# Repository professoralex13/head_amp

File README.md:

# CosplayCore

TODO: Put information about it here

## IMPORTANT NOTES:
Main board V1.0 runs ADC data from a CODEC into GPIO12 which also serves as a strapping pin. This signal is pulled high by the CODEC resulting in the ESP32 booting with a flash chip voltage is 1.8V which is incorrect.
To work around this, the following command must be run:
```espefuse --port [PORT] burn-efuse XPD_SDIO_REG 1 XPD_SDIO_TIEH 1 XPD_SDIO_FORCE 1```

This overrides the strapping pin so the memory supply voltage is permenantly set at 3.3V.
Until this comand is run and the fuses are burned on the ESP32, it cannot be flashed with any code.

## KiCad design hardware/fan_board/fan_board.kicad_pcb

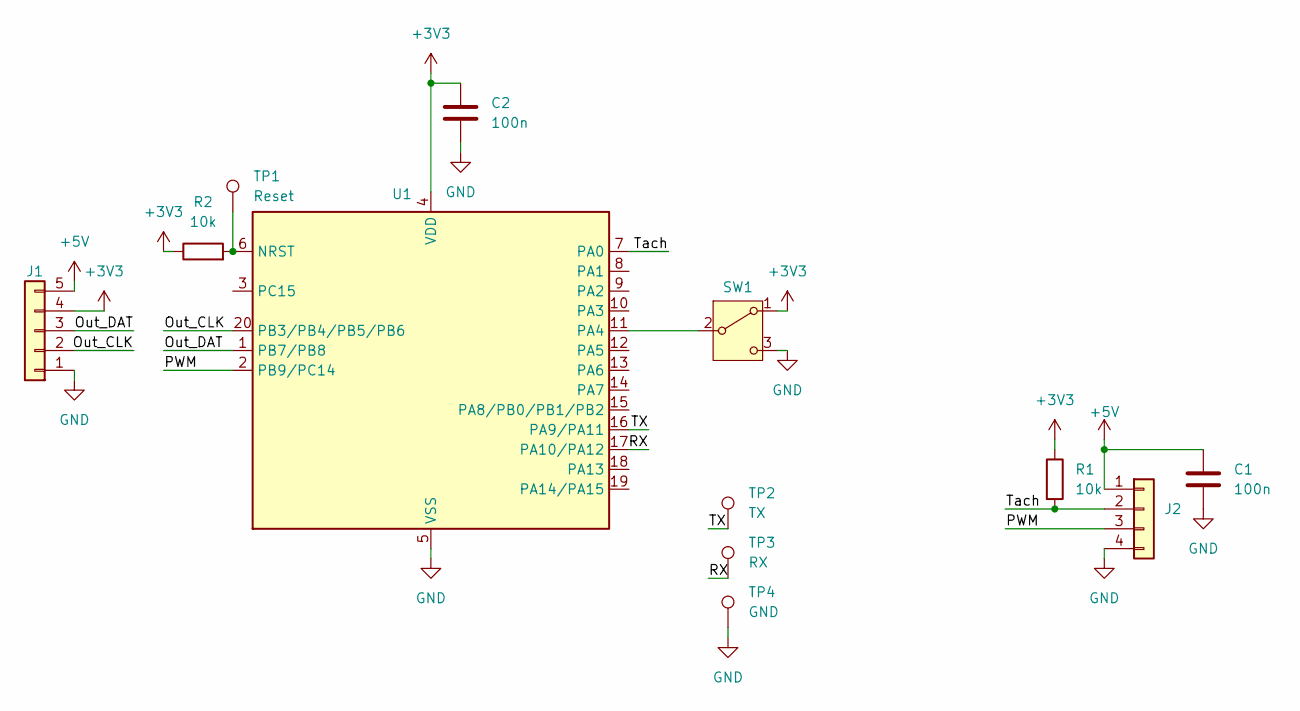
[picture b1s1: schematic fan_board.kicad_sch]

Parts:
C1, C2: 100n; C_1206_3216Metric_Pad1.33x1.80mm_HandSolder; LCSC C24497
J1: Conn_01x05; JST_EH_S5B-EH_1x05_P2.50mm_Horizontal; LCSC C265103
J2: Conn_01x04; JST_EH_S4B-EH_1x04_P2.50mm_Horizontal; LCSC C265068
R1, R2: 10k; R_1206_3216Metric_Pad1.30x1.75mm_HandSolder; LCSC C17902
SW1: SW_SPDT; Nidec_Copal_CAS-120A; LCSC C5619548
TP1: Reset; TestPoint_Pad_3.0x3.0mm
TP2: TX; TestPoint_Pad_3.0x3.0mm
TP3: RX; TestPoint_Pad_3.0x3.0mm
TP4: GND; TestPoint_Pad_3.0x3.0mm
U1: STM32G030F6Px; TSSOP-20_4.4x6.5mm_P0.65mm; LCSC C529330

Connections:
+3V3: C2.1, J1.4, R1.1, R2.1, SW1.1 (A), U1.4 (VDD)
+5V: C1.1, J1.5, J2.1
/Out_CLK: J1.2, U1.20 (PB3/PB4/PB5/PB6)
/Out_DAT: J1.3, U1.1 (PB7/PB8)
/PWM: J2.3, U1.2 (PB9/PC14)
/RX: TP3.1, U1.17 (PA10/PA12)
/TX: TP2.1, U1.16 (PA9/PA11)
/Tach: J2.2, R1.2, U1.7 (PA0)
GND: C1.2, C2.2, J1.1, J2.4, SW1.3 (C), TP4.1, U1.5 (VSS)
unnamed: SW1.2 (B), U1.11 (PA4)
unnamed: R2.2, TP1.1, U1.6 (NRST)

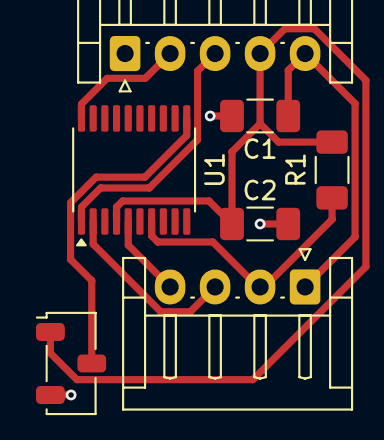
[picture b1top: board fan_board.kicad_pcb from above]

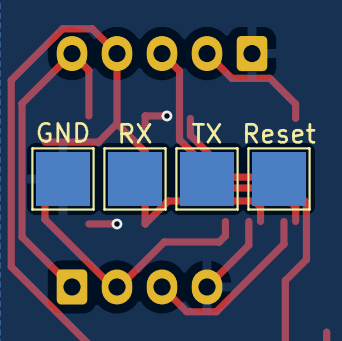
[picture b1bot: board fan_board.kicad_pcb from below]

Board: 2 copper layers, 11 parts (4 on the bottom side), 11 nets.

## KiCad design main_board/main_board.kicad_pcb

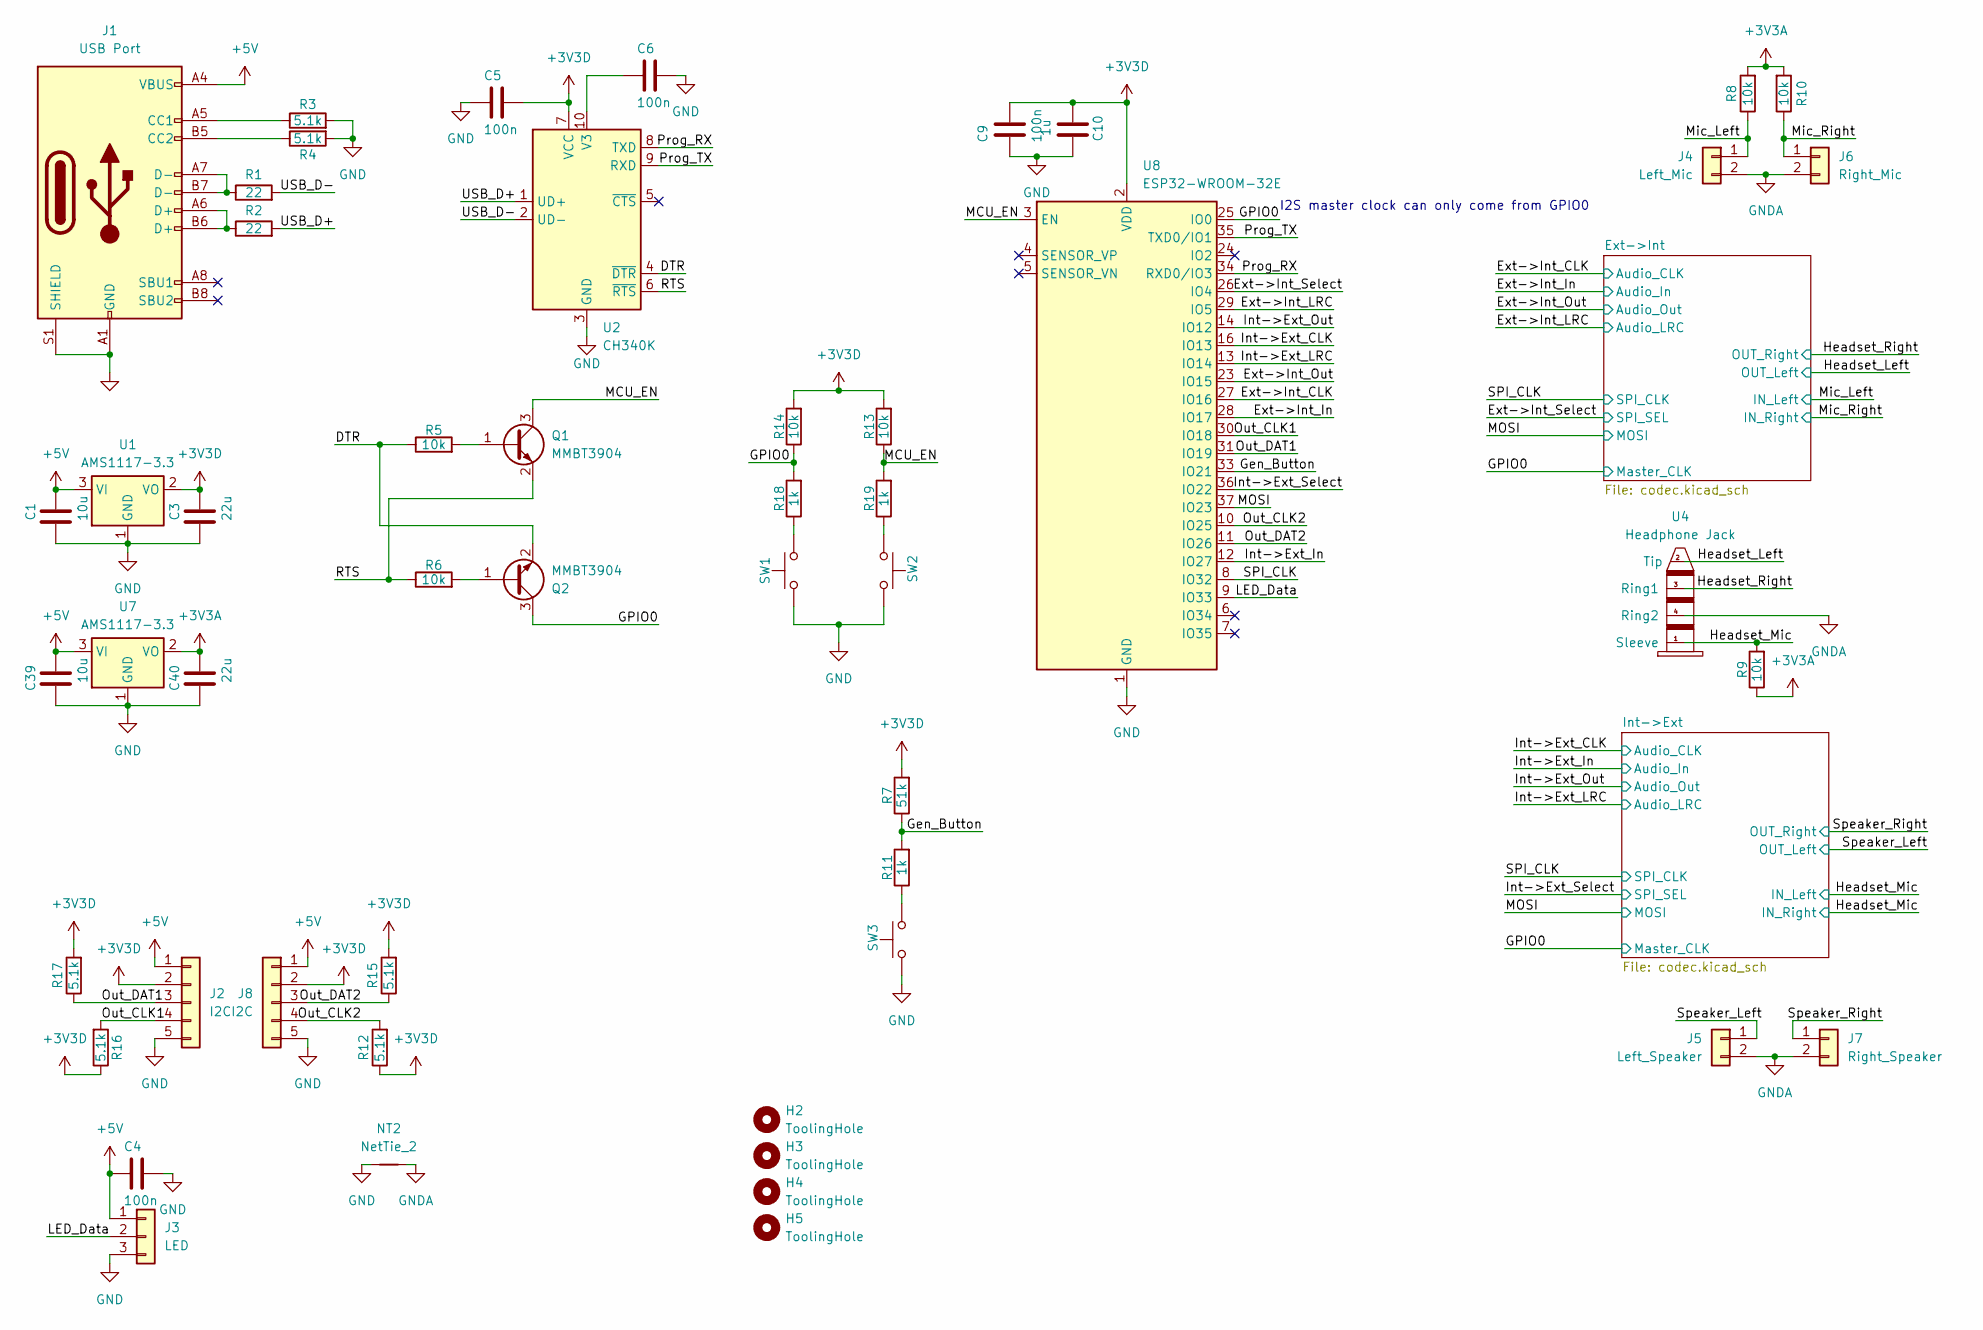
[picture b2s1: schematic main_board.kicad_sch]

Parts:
C1, C39: 10u; C_0603_1608Metric; LCSC C19702
C3, C40: 22u; C_0603_1608Metric; LCSC C59461
C4, C5, C6: 100n; C_0402_1005Metric; LCSC C307331
C9: 100n; C_0603_1608Metric; LCSC C14663
C10: 1u; C_0603_1608Metric; LCSC C15849
H2, H3, H4, H5: ToolingHole; ToolingHole_1.152mm
J1: USB Port; USB_C_Receptacle_GCT_USB4105-xx-A_16P_TopMnt_Horizontal; LCSC C2927038
J2, J8: I2C; JST_EH_S5B-EH_1x05_P2.50mm_Horizontal; LCSC C265103
J3: LED; JST_EH_S3B-EH_1x03_P2.50mm_Horizontal; LCSC C263754
J4: Left_Mic; JST_EH_S2B-EH_1x02_P2.50mm_Horizontal; LCSC C514173
J5: Left_Speaker; JST_EH_S2B-EH_1x02_P2.50mm_Horizontal; LCSC C514173
J6: Right_Mic; JST_EH_S2B-EH_1x02_P2.50mm_Horizontal; LCSC C514173
J7: Right_Speaker; JST_EH_S2B-EH_1x02_P2.50mm_Horizontal; LCSC C514173
NT2: NetTie_2; NetTie-2_SMD_Pad2.0mm
Q1, Q2: MMBT3904; SOT-23; LCSC C20526
R1, R2: 22; R_0402_1005Metric; LCSC C25092
R3, R4, R12, R15, R16, R17: 5.1k; R_0402_1005Metric; LCSC C25905
R5, R6, R8, R9, R10, R13, R14: 10k; R_0402_1005Metric; LCSC C25744
R7: 51k; R_0402_1005Metric; LCSC C25794
R11, R18, R19: 1k; R_0402_1005Metric; LCSC C11702
SW1, SW2, SW3: SW_Push; SW_SPST_TS-1088-xR020; LCSC C720477
U1, U7: AMS1117-3.3; SOT-223-3_TabPin2; LCSC C6186
U2: CH340K; SSOP-10-1EP_3.9x4.9mm_P1mm_EP2.1x3.3mm; LCSC C18208922
U4: Headphone Jack; PJ-320A; LCSC C2884926
U8: ESP32-WROOM-32E; LCSC C701342

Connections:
+3V3A: C40.2, R8.2, R9.1, R10.2, U7.2 (VO); also elsewhere on the board
+3V3D: C3.2, C5.2, C9.2, C10.1, J2.2, J8.2, R7.2, R12.1, R13.2, R14.2, R15.2, R16.1, R17.2, U1.2 (VO), U2.7 (VCC), U8.2 (VDD); also elsewhere on the board
+5V: C1.2, C4.1, C39.2, J1.A4 (VBUS), J1.A9 (VBUS), J1.B4 (VBUS), J1.B9 (VBUS), J2.1, J3.1, J8.1, U1.3 (VI), U7.3 (VI)
/DTR: Q2.2 (E), R5.1, U2.4 (~DTR)
/Ext->Int_CLK: U8.27 (IO16); also elsewhere on the board
/Ext->Int_In: U8.28 (IO17); also elsewhere on the board
/Ext->Int_LRC: U8.29 (IO5); also elsewhere on the board
/Ext->Int_Out: U8.23 (IO15); also elsewhere on the board
/Ext->Int_Select: U8.26 (IO4); also elsewhere on the board
/GPIO0: Q2.3 (C), R14.1, R18.2, U8.25 (IO0); also elsewhere on the board
/Gen_Button: R7.1, R11.2, U8.33 (IO21)
/Headset_Left: U4.2 (Tip); also elsewhere on the board
/Headset_Mic: R9.2, U4.1 (Sleeve); also elsewhere on the board
/Headset_Right: U4.3 (Ring1); also elsewhere on the board
/Int->Ext_CLK: U8.16 (IO13); also elsewhere on the board
/Int->Ext_In: U8.12 (IO27); also elsewhere on the board
/Int->Ext_LRC: U8.13 (IO14); also elsewhere on the board
/Int->Ext_Out: U8.14 (IO12); also elsewhere on the board
/Int->Ext_Select: U8.36 (IO22); also elsewhere on the board
/LED_Data: J3.2, U8.9 (IO33)
/MCU_EN: Q1.3 (C), R13.1, R19.2, U8.3 (EN)
/MOSI: U8.37 (IO23); also elsewhere on the board
/Mic_Left: J4.1, R8.1; also elsewhere on the board
/Mic_Right: J6.1, R10.1; also elsewhere on the board
/Out_CLK1: J2.4, R16.2, U8.30 (IO18)
/Out_CLK2: J8.4, R12.2, U8.10 (IO25)
/Out_DAT1: J2.3, R17.1, U8.31 (IO19)
/Out_DAT2: J8.3, R15.1, U8.11 (IO26)
/Prog_RX: U2.8 (TXD), U8.34 (RXD0/IO3)
/Prog_TX: U2.9 (RXD), U8.35 (TXD0/IO1)
/RTS: Q1.2 (E), R6.1, U2.6 (~RTS)
/SPI_CLK: U8.8 (IO32); also elsewhere on the board
/Speaker_Left: J5.1; also elsewhere on the board
/Speaker_Right: J7.1; also elsewhere on the board
/USB_D+: R2.2, U2.1 (UD+)
/USB_D-: R1.2, U2.2 (UD-)
GND: C1.1, C3.1, C4.2, C5.1, C6.2, C9.1, C10.2, C39.1, C40.1, J1.A1 (GND), J1.A12 (GND), J1.B1 (GND), J1.B12 (GND), J1.S1 (SHIELD), J2.5, J3.3, J8.5, NT2.1, R3.2, R4.2, SW1.1, SW2.1, SW3.1, U1.1 (GND), U2.3 (GND), U2.11 (GND), U7.1 (GND), U8.1 (GND), U8.15 (GND), U8.38 (GND), U8.39 (GND); also elsewhere on the board
GNDA: J4.2, J5.2, J6.2, J7.2, NT2.2, U4.4 (Ring2); also elsewhere on the board
unnamed: J1.A5 (CC1), R3.1
unnamed: J1.B5 (CC2), R4.1
unnamed: J1.A6 (D+), J1.B6 (D+), R2.1
unnamed: J1.A7 (D-), J1.B7 (D-), R1.1
unnamed: Q1.1 (B), R5.2
unnamed: Q2.1 (B), R6.2
unnamed: R11.1, SW3.2
unnamed: R18.1, SW1.2
unnamed: R19.1, SW2.2
unnamed: C6.1, U2.10 (V3)

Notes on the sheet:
I2S master clock can only come from GPIO0

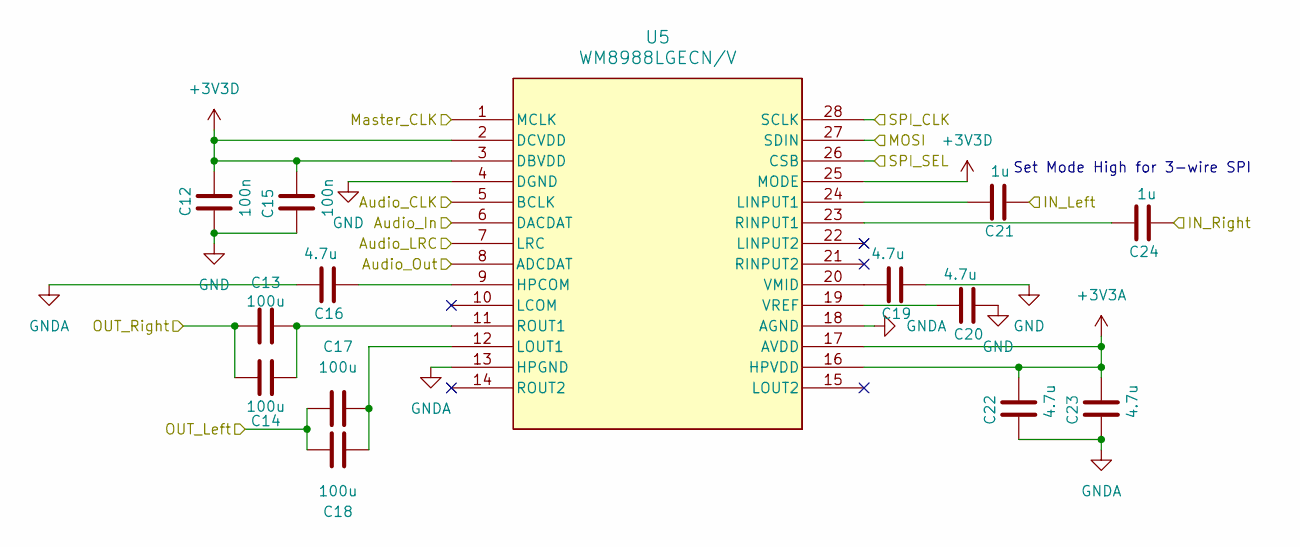
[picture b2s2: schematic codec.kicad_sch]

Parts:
C12, C15: 100n; C_0402_1005Metric; LCSC C307331
C13, C14, C17, C18: 100u; C_1206_3216Metric; LCSC C15008
C16, C19, C20, C22, C23: 4.7u; C_0402_1005Metric; LCSC C23733
C21, C24: 1u; C_0402_1005Metric; LCSC C52923
U5: WM8988LGECN/V; QFN28_4X4_CIR; LCSC C323851

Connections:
+3V3A: C22.2, C23.2, U5.16 (HPVDD), U5.17 (AVDD); also elsewhere on the board
+3V3D: C12.2, C15.2, U5.2 (DCVDD), U5.3 (DBVDD), U5.25 (MODE); also elsewhere on the board
/GPIO0: U5.1 (MCLK); also elsewhere on the board
/Headset_Mic: C21.1, C24.1; also elsewhere on the board
/Int->Ext_CLK: U5.5 (BCLK); also elsewhere on the board
/Int->Ext_In: U5.6 (DACDAT); also elsewhere on the board
/Int->Ext_LRC: U5.7 (LRC); also elsewhere on the board
/Int->Ext_Out: U5.8 (ADCDAT); also elsewhere on the board
/Int->Ext_Select: U5.26 (CSB); also elsewhere on the board
/MOSI: U5.27 (SDIN); also elsewhere on the board
/SPI_CLK: U5.28 (SCLK); also elsewhere on the board
/Speaker_Left: C17.1, C18.1; also elsewhere on the board
/Speaker_Right: C13.1, C14.1; also elsewhere on the board
GND: C12.1, C15.1, C19.1, C20.1, U5.4 (DGND); also elsewhere on the board
GNDA: C16.2, C22.1, C23.1, U5.13 (HPGND), U5.18 (AGND); also elsewhere on the board
unnamed: C16.1, U5.9 (HPCOM)
unnamed: C21.2, U5.24 (LINPUT1)
unnamed: C17.2, C18.2, U5.12 (LOUT1)
unnamed: C24.2, U5.23 (RINPUT1)
unnamed: C13.2, C14.2, U5.11 (ROUT1)
unnamed: C19.2, U5.20 (VMID)
unnamed: C20.2, U5.19 (VREF)

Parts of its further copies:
C25, C28: 100n; C_0402_1005Metric; LCSC C307331
C26, C27, C30, C31: 100u; C_1206_3216Metric; LCSC C15008
C29, C32, C33, C35, C36: 4.7u; C_0402_1005Metric; LCSC C23733
C34, C37: 1u; C_0402_1005Metric; LCSC C52923
U6: WM8988LGECN/V; QFN28_4X4_CIR; LCSC C323851

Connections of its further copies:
+3V3A: C35.2, C36.2, U6.16 (HPVDD), U6.17 (AVDD); also elsewhere on the board
+3V3D: C25.2, C28.2, U6.2 (DCVDD), U6.3 (DBVDD), U6.25 (MODE); also elsewhere on the board
/Ext->Int_CLK: U6.5 (BCLK); also elsewhere on the board
/Ext->Int_In: U6.6 (DACDAT); also elsewhere on the board
/Ext->Int_LRC: U6.7 (LRC); also elsewhere on the board
/Ext->Int_Out: U6.8 (ADCDAT); also elsewhere on the board
/Ext->Int_Select: U6.26 (CSB); also elsewhere on the board
/GPIO0: U6.1 (MCLK); also elsewhere on the board
/Headset_Left: C30.1, C31.1; also elsewhere on the board
/Headset_Right: C26.1, C27.1; also elsewhere on the board
/MOSI: U6.27 (SDIN); also elsewhere on the board
/Mic_Left: C34.1; also elsewhere on the board
/Mic_Right: C37.1; also elsewhere on the board
/SPI_CLK: U6.28 (SCLK); also elsewhere on the board
GND: C25.1, C28.1, C32.1, C33.1, U6.4 (DGND); also elsewhere on the board
GNDA: C29.2, C35.1, C36.1, U6.13 (HPGND), U6.18 (AGND); also elsewhere on the board
unnamed: C29.1, U6.9 (HPCOM)
unnamed: C34.2, U6.24 (LINPUT1)
unnamed: C30.2, C31.2, U6.12 (LOUT1)
unnamed: C37.2, U6.23 (RINPUT1)
unnamed: C26.2, C27.2, U6.11 (ROUT1)
unnamed: C32.2, U6.20 (VMID)
unnamed: C33.2, U6.19 (VREF)

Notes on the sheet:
Set Mode High for 3-wire SPI

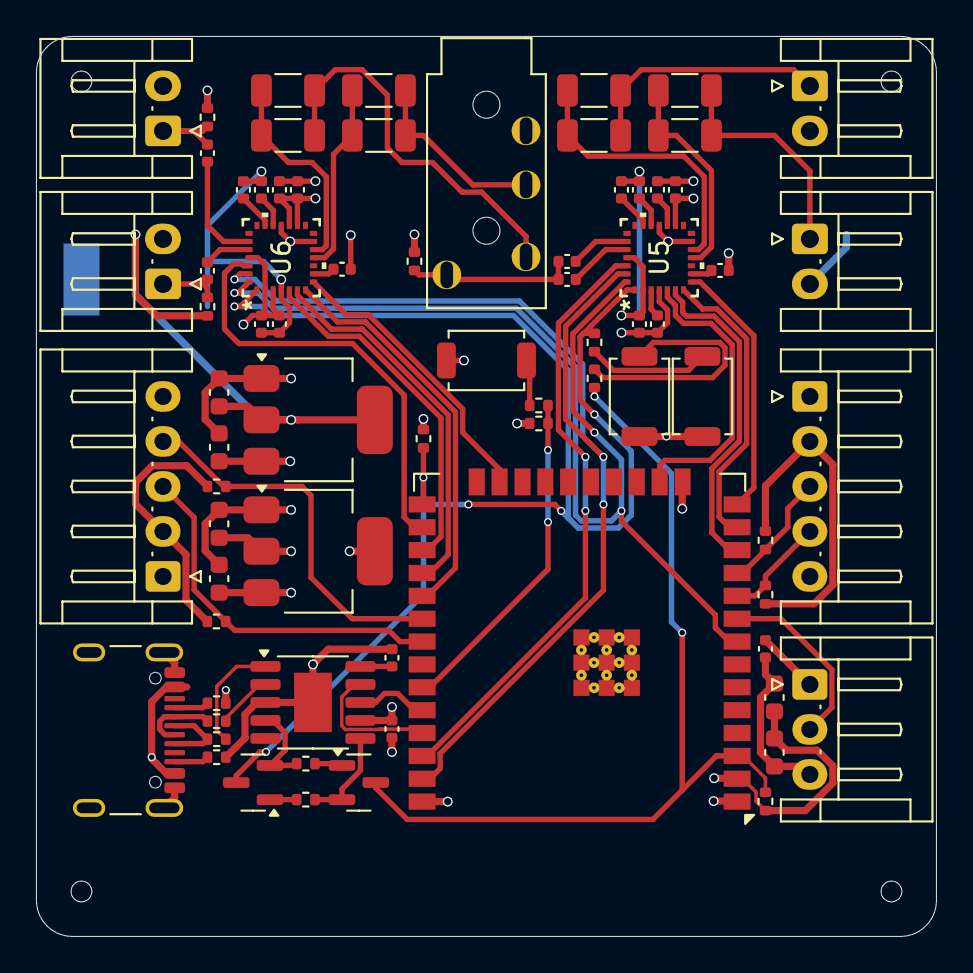
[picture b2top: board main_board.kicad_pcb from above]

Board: 4 copper layers, 50.0 x 50.0 mm, 79 parts (1 on the bottom side), 62 nets.

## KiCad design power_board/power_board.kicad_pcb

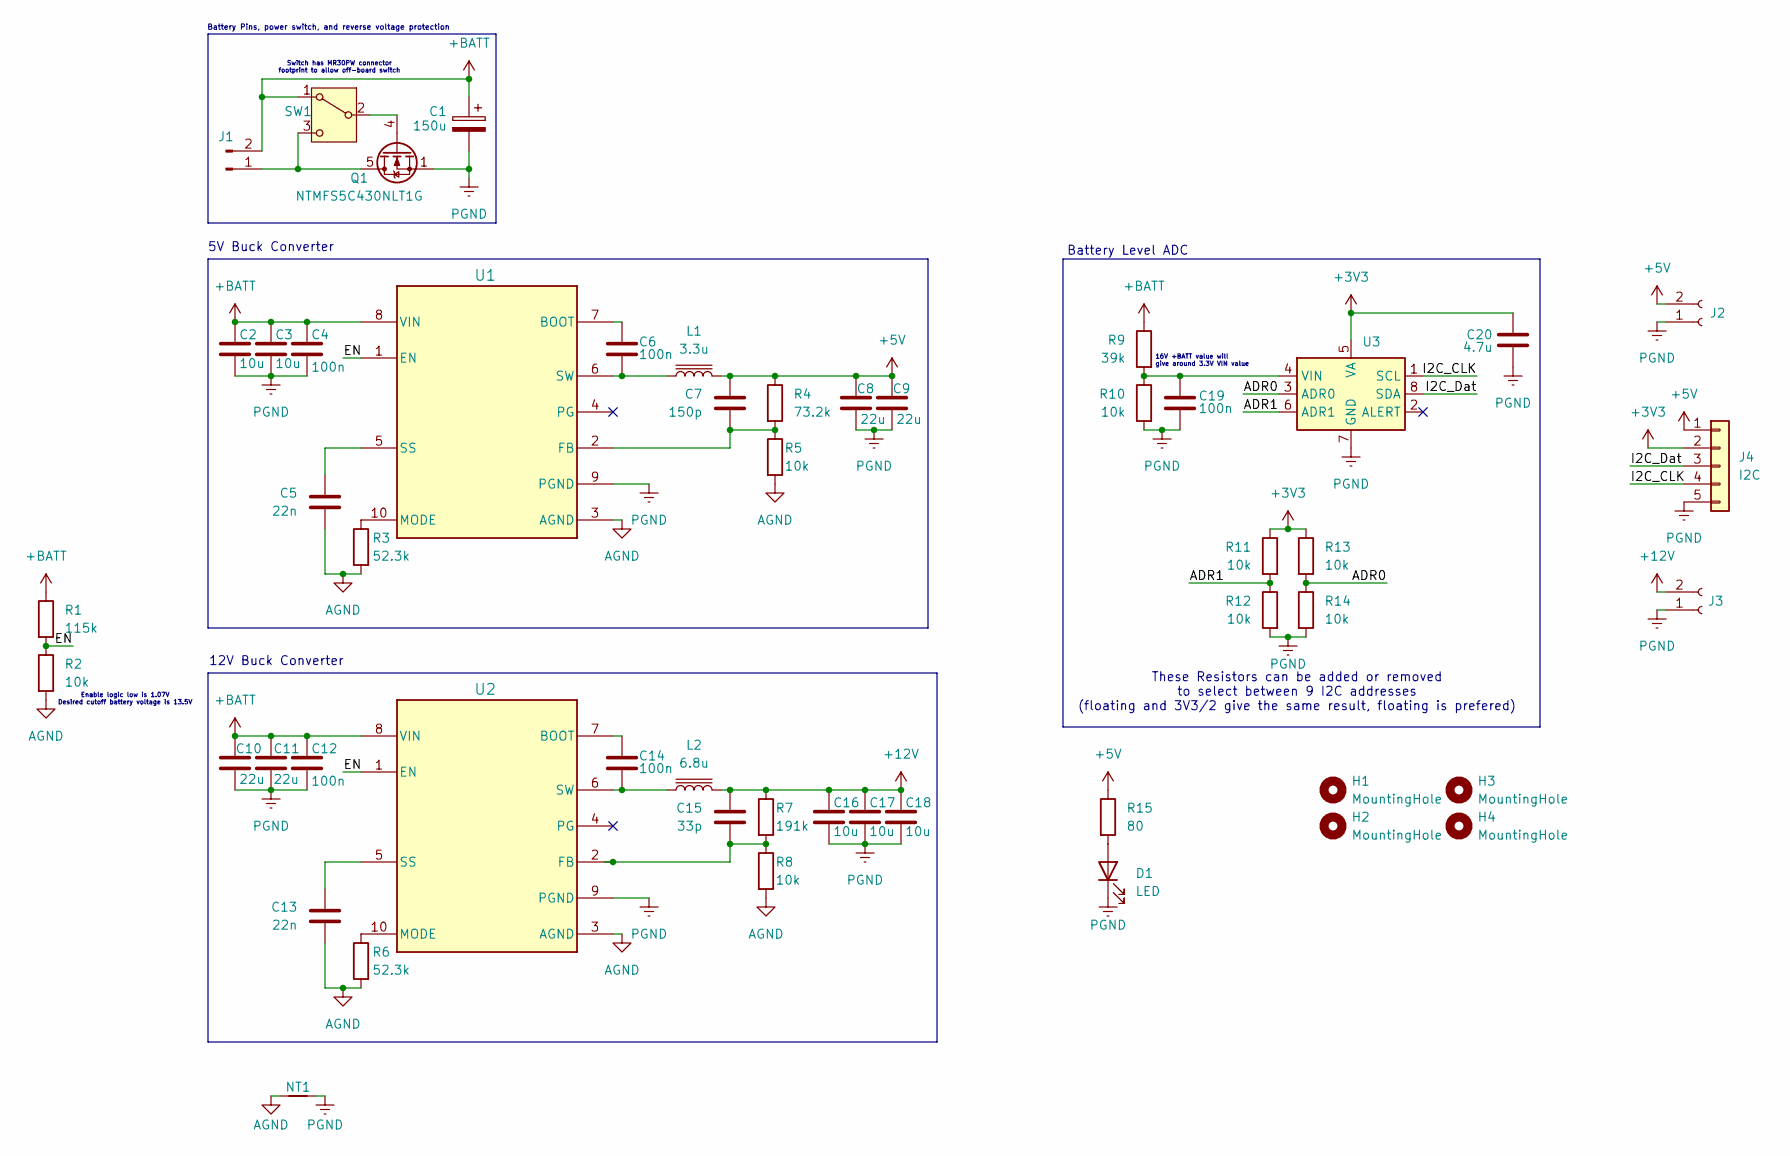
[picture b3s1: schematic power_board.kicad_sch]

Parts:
C1: 150u; CP_Elec_6.3x7.7; LCSC C2895737
C2, C3, C16, C17, C18: 10u; C_0805_2012Metric; LCSC C5137488
C4, C6, C12, C14: 100n; C_0805_2012Metric; LCSC C5137467
C5, C13: 22n; C_0805_2012Metric; LCSC C5137639
C7: 150p; C_0805_2012Metric; LCSC C7467159
C8, C9, C10, C11: 22u; C_0805_2012Metric; LCSC C7419435
C15: 33p; C_0805_2012Metric; LCSC C7419432
C19: 100n; C_0805_2012Metric; LCSC C476766
C20: 4.7u; C_0805_2012Metric; LCSC C47117445
D1: LED; LED_1206_3216Metric; LCSC C965825
H1, H2, H3, H4: MountingHole; MountingHole_3.2mm_M3
J1: Conn_01x02_Pin; AMASS_XT60PW-M_1x02_P7.20mm_Horizontal; LCSC C98732
J2, J3: Conn_01x02_Socket; AMASS_XT30PW-F_1x02_P2.50mm_Horizontal; LCSC C2913282
J4: I2C; JST_EH_S5B-EH_1x05_P2.50mm_Horizontal; LCSC C265103
L1: 3.3u; L_APV_APH1030; LCSC C845075
L2: 6.8u; L_TaiTech_TMPC1265_13.5x12.5mm; LCSC C2847562
NT1: NetTie_2; NetTie-2_SMD_Pad0.5mm
Q1: NTMFS5C430NLT1G; ONSemi_SO-8FL_488AA; LCSC C36499169
R1: 115k; R_0805_2012Metric; LCSC C2933289
R2, R5, R8, R10: 10k; R_0805_2012Metric; LCSC C2907219
R3, R6: 52.3k; R_0805_2012Metric; LCSC C2933465
R4: 73.2k; R_0805_2012Metric; LCSC C5713314
R7: 191k; R_0805_2012Metric; LCSC C3000728
R9: 39k; R_0805_2012Metric; LCSC C2933691
R11, R12, R13, R14: 10k; R_1206_3216Metric; LCSC C2907423
R15: 80; R_1206_3216Metric; LCSC C2907540
SW1: SW_SPDT; AMASS_MR30PW-FB_1x03_P3.50mm_Horizontal; LCSC C19268035
U1, U2: TPS56A37RPAR; RPA0010A-MFG; LCSC C22392669
U3: ADC081C021CIMM; MSOP-8_3x3mm_P0.65mm; LCSC C206013

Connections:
+3V3: C20.1, J4.2, R11.1, R13.1, U3.5 (VA)
+5V: C7.1, C8.1, C9.1, J2.2, J4.1, L1.2, R4.1, R15.1
+12V: C15.1, C16.1, C17.1, C18.1, J3.2, L2.2, R7.1
+BATT: C1.1, C2.1, C3.1, C4.1, C10.1, C11.1, C12.1, J1.2, R1.1, R9.1, SW1.1 (A), U1.8 (VIN), U2.8 (VIN)
/ADR0: R13.2, R14.1, U3.3 (ADR0)
/ADR1: R11.2, R12.1, U3.6 (ADR1)
/EN: R1.2, R2.1, U1.1 (EN), U2.1 (EN)
/I2C_CLK: J4.4, U3.1 (SCL)
/I2C_Dat: J4.3, U3.8 (SDA)
AGND: C5.2, C13.2, NT1.1, R2.2, R3.2, R5.2, R6.2, R8.2, U1.3 (AGND), U2.3 (AGND)
unnamed: D1.2 (A), R15.2
unnamed: J1.1, Q1.5 (D), SW1.3 (C)
unnamed: Q1.4 (G), SW1.2 (B)
unnamed: C6.2, U1.7 (BOOT)
unnamed: C7.2, R4.2, R5.1, U1.2 (FB)
unnamed: R3.1, U1.10 (MODE)
unnamed: C5.1, U1.5 (SS)
unnamed: C6.1, L1.1, U1.6 (SW)
unnamed: C14.2, U2.7 (BOOT)
unnamed: C15.2, R7.2, R8.1, U2.2 (FB)
unnamed: R6.1, U2.10 (MODE)
unnamed: C13.1, U2.5 (SS)
unnamed: C14.1, L2.1, U2.6 (SW)
unnamed: C19.2, R9.2, R10.1, U3.4 (VIN)
PGND: C1.2, C2.2, C3.2, C4.2, C8.2, C9.2, C10.2, C11.2, C12.2, C16.2, C17.2, C18.2, C19.1, C20.2, D1.1 (K), J2.1, J3.1, J4.5, NT1.2, Q1.1 (S), Q1.2 (S), Q1.3 (S), R10.2, R12.2, R14.2, U1.9 (PGND), U2.9 (PGND), U3.7 (GND)

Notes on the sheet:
5V Buck Converter
Battery Level ADC
Switch has MR30PW connector footprint to allow off-board switch
12V Buck Converter
These Resistors can be added or removed to select between 9 I2C addresses (floating and 3V3/2 give the same result, floating is prefered)
16V +BATT value will give around 3.3V VIN value
Enable logic low is 1.07V Desired cutoff battery voltage is 13.5V
Battery Pins, power switch, and reverse voltage protection

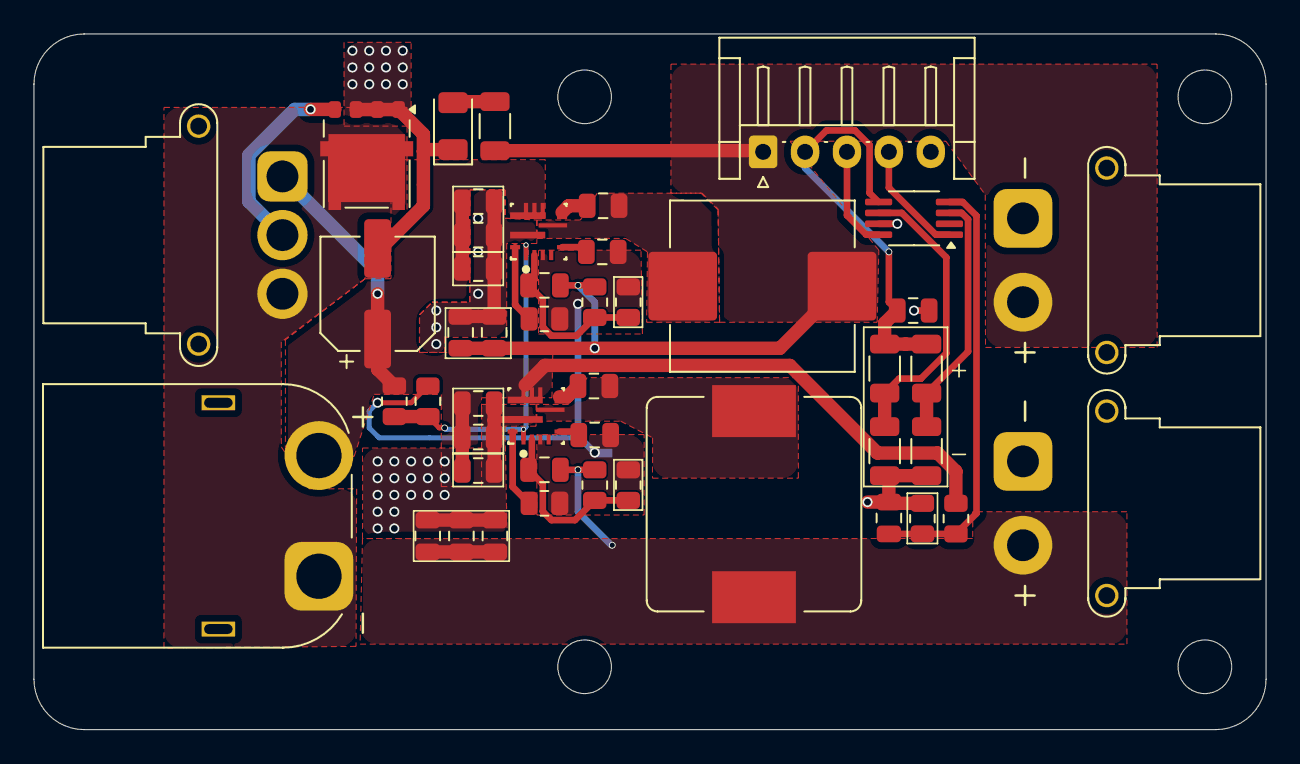
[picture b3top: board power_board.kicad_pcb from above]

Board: 2 copper layers, 73.5 x 41.5 mm, 52 parts (1 on the bottom side), 25 nets.

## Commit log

2025-09-09 Initial
2025-09-09 Route PCB :3
2025-10-27 Lots of stuff
2025-10-28 More stuff
2025-10-28 Fixes
2025-10-28 started compact layout
2025-10-29 feat: start hat version
2025-10-30 More capacitor layed
2025-10-30 Remove conflict silkscreen
2025-11-01 feat: pretty much done
2025-11-01 silkscreen
2025-11-03 feat: overhaul
2025-11-06 add 3d models and tooling holes
2025-11-06 compactify
2025-11-06 Add holes and generic control button
2025-11-25 Add second expansion port
2025-11-25 Remove unused libraries
2025-11-25 Remove libraries from tables
2025-11-25 Move to subproject
2025-11-25 fix: missing I2C pullup resistors
2025-12-06 Started breakout boards
2025-12-20 finish v1.0
2025-12-26 feat: initial power board
2025-12-26 feat: 10A converters
2025-12-27 larger power traces
2025-12-27 improve power fill thickness
2026-01-01 Add README
    Added important notes regarding the main board V1.0 and ADC data handling.
2026-01-02 feat: basic codec control
2026-01-02 reroute SPI (non output pin issue)
2026-01-02 refactor: organized register set functions
2026-01-02 feat: I2S interface
2026-01-02 feat: bluetooth
2026-01-04 restructure: split into hardware and firmware folders
2026-01-04 initialize app
